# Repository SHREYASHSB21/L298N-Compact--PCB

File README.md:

# L298N Compact Motor Driver PCB

Compact L298N motor driver PCB with integrated 7805 regulator and flyback diode protection using KiCad

## Features

- Size 84.58 mm x 20 mm
- Compact single-layer layout
- Integrated 7805 voltage regulator
- External flyback diode protection
- Screw terminals for motors and power
- 5V indicator LED
- Easy header interface for microcontrollers

## Software

- KiCad 9

## Applications

The **L298N Compact Motor Driver PCB** is a plug-and-play dual H-Bridge motor driver designed for seamless integration with microcontrollers such as **Arduino, ESP32, STM32, and Raspberry Pi Pico**. Simply connect the power supply, motor outputs, and control pins to quickly drive two DC motors without additional motor driver circuitry.

### Suitable Applications

- Line Following Robots
- Obstacle Avoiding Robots
- Bluetooth Controlled Robots
- Wi-Fi Controlled Robots
- Autonomous Mobile Robots (AMRs)
- Differential Drive Robots
- Small Robotic Cars
- Educational Robotics Projects
- Embedded Systems Prototyping
- General-purpose Dual DC Motor Control
- DIY Electronics and Robotics Projects

## Author

-Shreyash Birdawade

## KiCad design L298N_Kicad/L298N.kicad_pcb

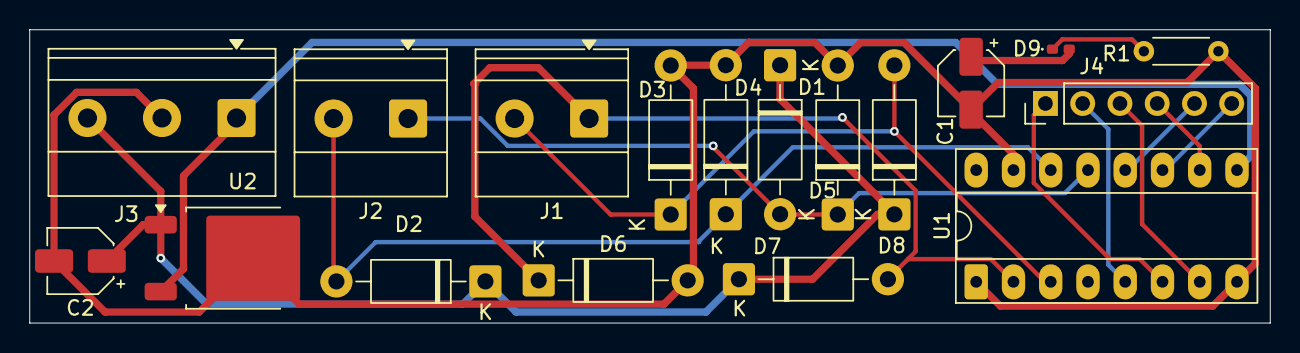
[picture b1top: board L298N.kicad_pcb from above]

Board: 2 copper layers, 84.6 x 20.0 mm, 18 parts (0 on the bottom side), 14 nets.

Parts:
C1, C2: C; CP_Elec_4x3
D1, D2, D3, D4, D5, D6, D7, D8: 1N4004; D_DO-41_SOD81_P10.16mm_Horizontal
D9: LED; LED_0402_1005Metric_Pad0.77x0.64mm_HandSolder
J1, J2: Screw_Terminal_01x02; TerminalBlock_Phoenix_MKDS-1,5-2-5.08_1x02_P5.08mm_Horizont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
J3: Screw_Terminal_01x03; TerminalBlock_Phoenix_MKDS-1,5-3-5.08_1x03_P5.08mm_Horizont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
J4: Conn_01x06_Pin; PinHeader_1x06_P2.54mm_Vertical
R1: R; R_Axial_DIN0204_L3.6mm_D1.6mm_P5.08mm_Horizontal
U1: L298HN; DIP-16_W7.62mm_Socket_LongPads
U2: L7805; TO-252-2

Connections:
5V Vcc: C1.1, D9.2 (A), J3.1, U1.9 (Vss), U2.3 (OUT)
12V input: C2.1, D1.1 (K), D2.1 (K), D7.1 (K), D8.1 (K), J3.3, U2.1 (IN)
GND: C1.2, C2.2, D3.2 (A), D4.2 (A), D5.2 (A), D6.2 (A), J3.2, R1.2, U1.1 (SENSE_A), U1.8 (GND), U1.15 (SENSE_B), U2.2 (GND)
unnamed: D9.1 (K), R1.1
en1: J4.1, U1.6 (EnA)
en2: J4.6, U1.11 (EnB)
in1_1: J4.2, U1.5 (IN1)
in1_2: J4.3, U1.7 (IN2)
in2_1: J4.4, U1.10 (IN3)
in2_2: J4.5, U1.12 (IN4)
m1_1: D6.1 (K), D7.2 (A), J1.1, U1.2 (OUT1)
m1_2: D3.1 (K), D8.2 (A), J1.2, U1.3 (OUT2)
m2_1: D1.2 (A), D5.1 (K), J2.1, U1.13 (OUT3)
m2_2: D2.2 (A), D4.1 (K), J2.2, U1.14 (OUT4)
